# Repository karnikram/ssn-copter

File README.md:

<h1 align="center">SSNCopter</h1>

A 3 axis flight controller using an ATMega 328 and a 3 axis L3G4200D gyro. 
Uses pin change interrupts, I2C comm, PWM and 3 PID rate control loops, all working together with an update rate of ~250 Hz.

Also included are the PCB files for the controller.

<table>
  <tr>
    <td width = "50%"></td>
    <td width = "50%"></td>
  </tr>

</table>

Based on Joop Brokking's [YMFC-3D](http://www.brokking.net/ymfc-3d_main.html) project.

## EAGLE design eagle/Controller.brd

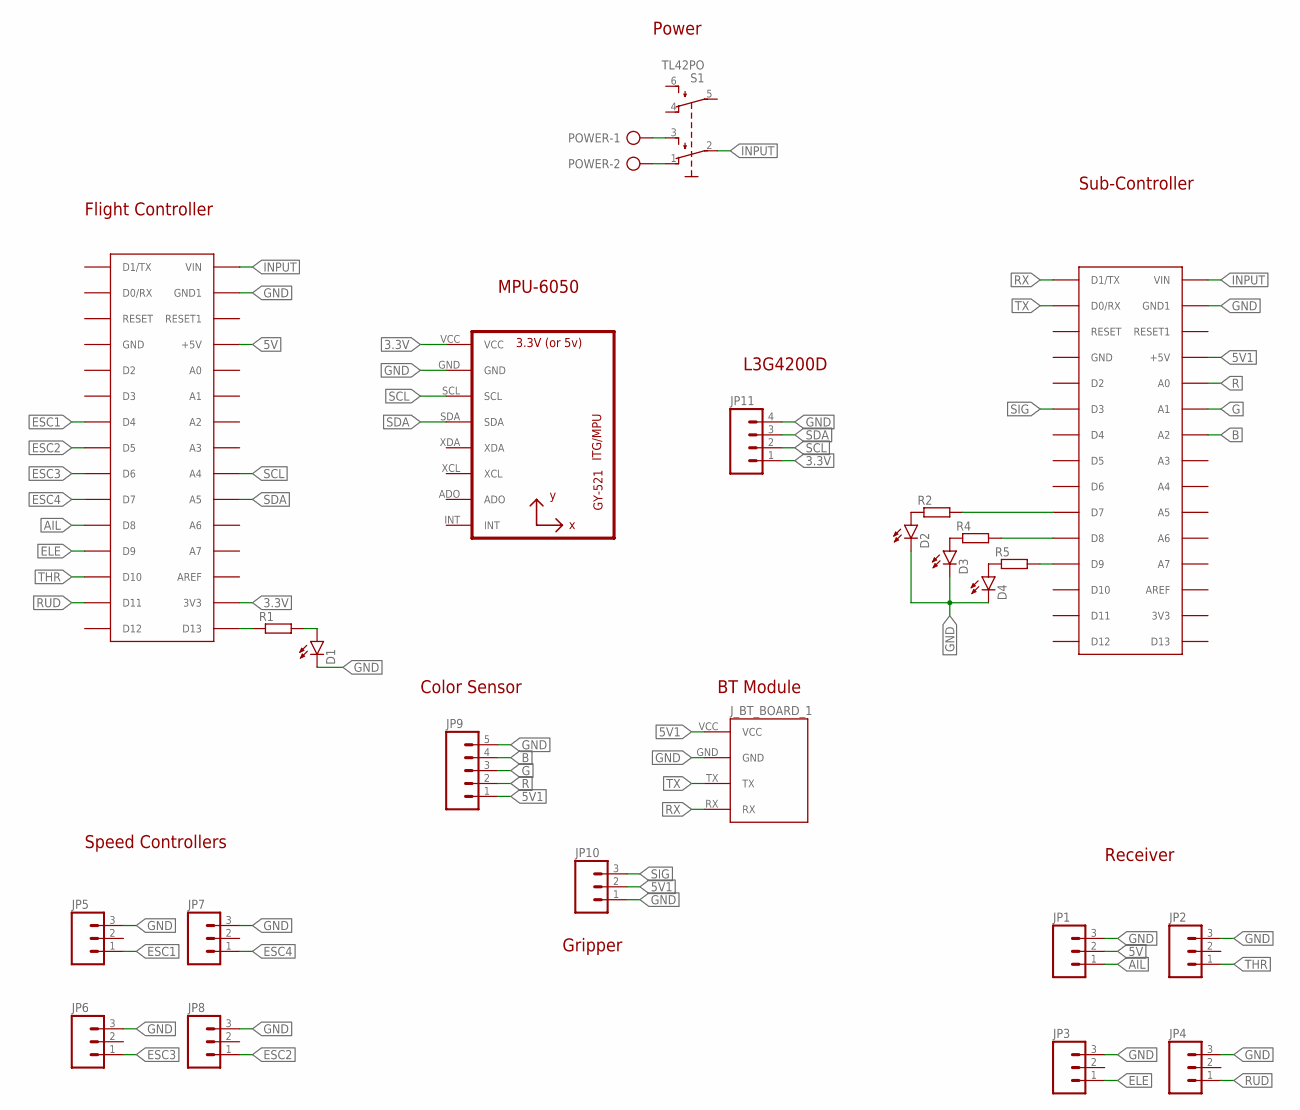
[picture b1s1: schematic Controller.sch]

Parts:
D1, D2, D3, D4: LED5MM
JP1, JP2, JP3, JP4, JP5, JP6, JP7, JP8, JP10: M031X03_NO_SILK; 1X03_NO_SILK
JP9: M05NO_SILK; 1X05_NO_SILK
JP11: M04NO_SILK_ALL_ROUND; 1X04_NO_SILK_ALL_ROUND
J_BT_BOARD_1: BLUETOOTH_BOARDSTANDING; BT_BOARD_FOOTPRINT_STANDING
POWER: AK300/2
R1, R2, R4, R5: R-EU_0207/10; 0207/10
S1: TL42PO; TL4XPO
U1: GY-521MPU6050; GY-521
U$1, U$2: ARDUINONANO; PDIP-32

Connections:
3.3V: JP11.1, U1.VCC, U$1.3V3
5V: JP1.2, U$1.+5V
5V1: JP9.1, JP10.2, J_BT_BOARD_1.VCC, U$2.+5V
AIL: JP1.1, U$1.D8
B: JP9.4, U$2.A2
ELE: JP3.1, U$1.D9
ESC1: JP5.1, U$1.D4
ESC2: JP8.1, U$1.D5
ESC3: JP6.1, U$1.D6
ESC4: JP7.1, U$1.D7
G: JP9.3, U$2.A1
GND: D1.K (C), D2.K (C), D3.K (C), D4.K (C), JP1.3, JP2.3, JP3.3, JP4.3, JP5.3, JP6.3, JP7.3, JP8.3, JP9.5, JP10.1, JP11.4, J_BT_BOARD_1.GND, POWER.1, S1.3 (S), U1.GND, U$1.GND1, U$2.GND1
INPUT: S1.2, U$1.VIN, U$2.VIN
N: POWER.2, S1.1 (O)
unnamed: R1.1, U$1.D13
unnamed: D1.A, R1.2
unnamed: R2.2, U$2.D7
unnamed: R4.2, U$2.D8
unnamed: R5.2, U$2.D9
unnamed: D2.A, R2.1
unnamed: D3.A, R4.1
unnamed: D4.A, R5.1
R: JP9.2, U$2.A0
RUD: JP4.1, U$1.D11
RX: J_BT_BOARD_1.RX, U$2.D1/TX
SCL: JP11.2, U1.SCL, U$1.A4
SDA: JP11.3, U1.SDA, U$1.A5
SIG: JP10.3, U$2.D3
THR: JP2.1, U$1.D10
TX: J_BT_BOARD_1.TX, U$2.D0/RX

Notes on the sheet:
Flight Controller
Power
MPU-6050
Color Sensor
BT Module
Speed Controllers
Receiver
Sub-Controller
Gripper
L3G4200D

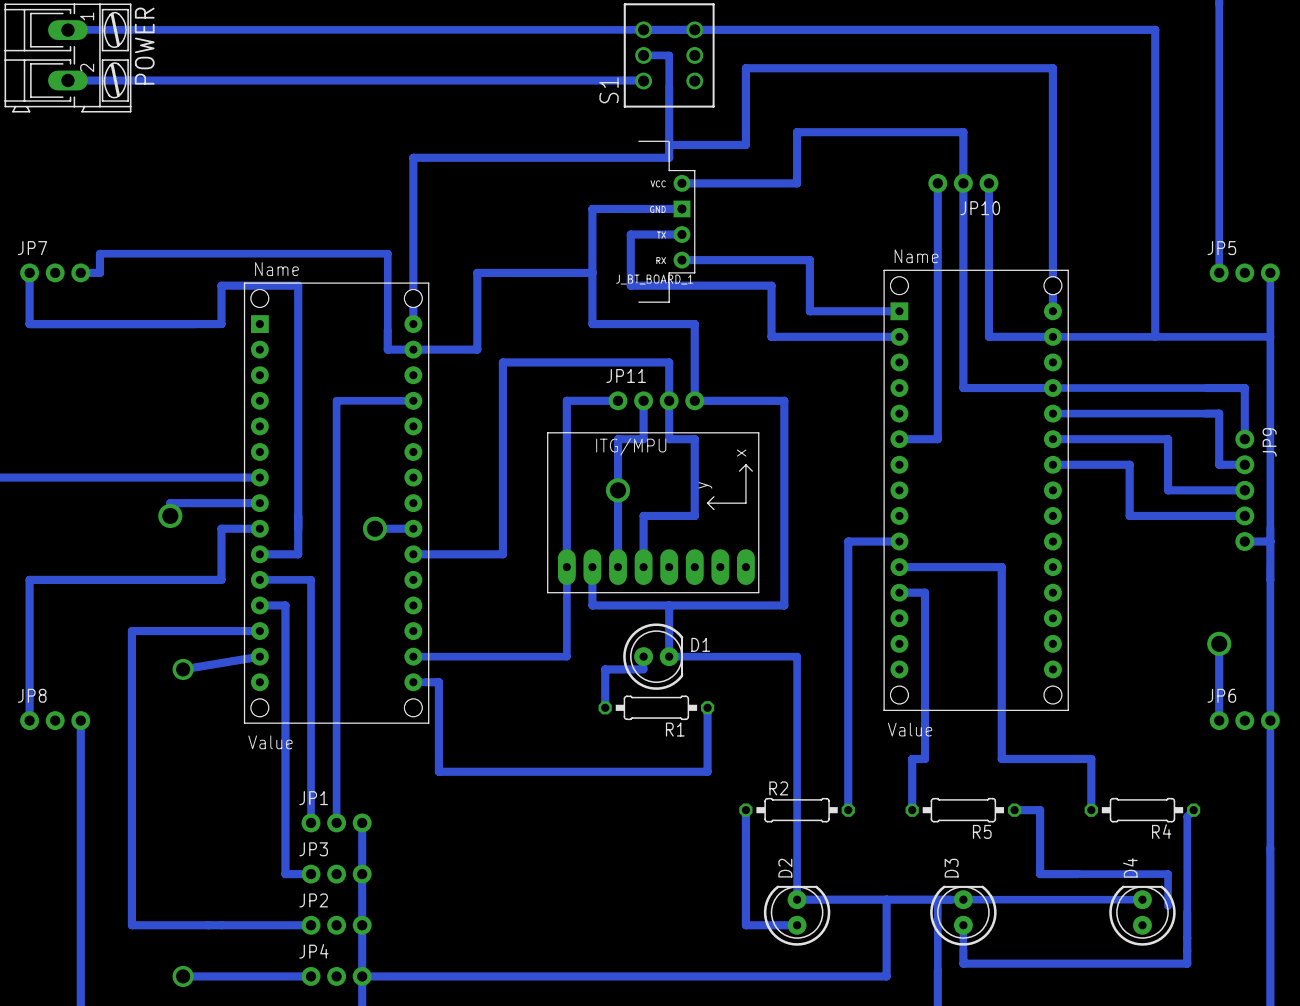
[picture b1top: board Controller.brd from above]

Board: 2 copper layers, 25 parts (0 on the bottom side), 30 nets.

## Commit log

2015-12-09 Test
2018-09-27 Clean commit history

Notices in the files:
parts and their libraries:
SparkFun-LED: Licensing: Creative Commons ShareAlike 4.0 International - https://creativecommons.org/licenses/by-sa/4.0
